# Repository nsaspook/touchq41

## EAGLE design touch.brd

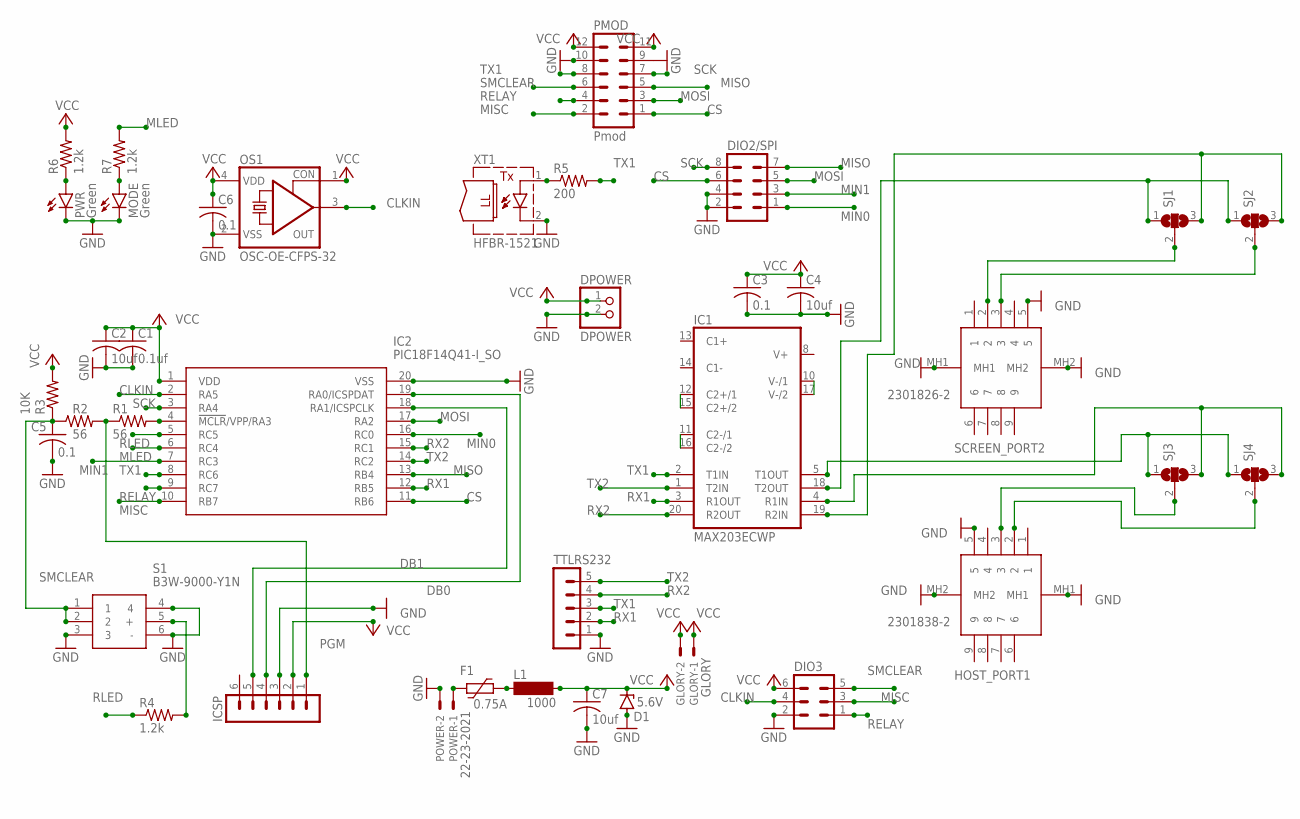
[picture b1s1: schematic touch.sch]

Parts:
C1: 0.1uf; C0805
C2, C4, C7: 10uf; C0805
C3, C5, C6: 0.1; C0805
D1: 5.6V; SMB
DIO2/SPI: MA04-2
DIO3: MA03-2
DPOWER: DPOWER; 1X02
F1: 0.75A; 1206L
GLORY: GLORY; 22-23-2021
HOST_PORT1: 2301838-2; 23018382
IC1: MAX203ECWP; SO20L
IC2: PIC18F14Q41-I_SO; SOIC127P1030X265-20N
ICSP: MA06-1
L1: 1000; SM-1206
MODE: Green; CHIPLED_1206
OS1: OSC-OE-CFPS-32; 7.2X5.2-4-PAD
PMOD: Pmod; MA06-2
POWER: 22-23-2021
PWR: Green; CHIPLED_1206
R1, R2: 56; R0805
R3: 10K; R0805
R4, R6, R7: 1.2k; R0805
R5: 200; R0805
S1: B3W-9000-Y1N; B3W-9_1-LED
SCREEN_PORT2: 2301826-2; 23018262
SJ1, SJ2, SJ3, SJ4: SJ2W; SJ_2
TTLRS232: MA05-1
XT1: HFBR-1521; HFBR-15X3

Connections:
CLKIN: DIO3.4, IC2.2 (RA5), OS1.3 (OUT)
CS: DIO2/SPI.6, IC2.11 (RB6), PMOD.1
DB0: IC2.19 (RA0/ICSPDAT), ICSP.4
DB1: IC2.18 (RA1/ICSPCLK), ICSP.5
GND: C1.2, C2.2, C3.2, C4.2, C5.2, C6.2, C7.2, D1.A, DIO2/SPI.2, DIO2/SPI.4, DIO3.2, DPOWER.2, HOST_PORT1.5, HOST_PORT1.MH1, HOST_PORT1.MH2, IC1.6 (GND), IC1.9 (GND), IC2.20 (VSS), ICSP.3, MODE.C, OS1.2 (VSS), PMOD.9, PMOD.10, POWER.2, PWR.C, S1.3, S1.4, S1.6 (-), SCREEN_PORT2.5, SCREEN_PORT2.MH1, SCREEN_PORT2.MH2, TTLRS232.1, XT1.2 (C)
MIN0: DIO2/SPI.1, IC2.16 (RC0)
MIN1: DIO2/SPI.3, IC2.7 (RC3)
MISC: DIO3.3, IC2.10 (RB7), PMOD.2
MISO: DIO2/SPI.7, IC2.13 (RB4), PMOD.5
MLED: IC2.6 (RC4), R7.2
MOSI: DIO2/SPI.5, IC2.17 (RA2), PMOD.3
unnamed: SCREEN_PORT2.3, SJ2.2
unnamed: SCREEN_PORT2.2, SJ1.2
unnamed: HOST_PORT1.2, SJ4.2
unnamed: HOST_PORT1.3, SJ3.2
unnamed: IC1.12 (C2+/1), IC1.15 (C2+/2)
unnamed: IC1.11 (C2-/1), IC1.16 (C2-/2)
unnamed: IC1.10 (V-/1), IC1.17 (V-/2)
unnamed: IC1.5 (T1OUT), SJ3.1, SJ4.1
unnamed: IC1.4 (R1IN), SJ3.3, SJ4.3
unnamed: IC1.18 (T2OUT), SJ1.1, SJ2.1
unnamed: IC1.19 (R2IN), SJ1.3, SJ2.3
unnamed: IC2.4 (!MCLR!/VPP/RA3), R1.2
unnamed: F1.2, POWER.1
unnamed: MODE.A, R7.1
unnamed: R4.2, S1.5 (+)
unnamed: R5.1, XT1.1 (A)
unnamed: F1.1, L1.1
unnamed: PWR.A, R6.1
PGM: ICSP.1, R1.1, R2.2
RELAY: DIO3.1, IC2.9 (RC7), PMOD.4
RLED: IC2.5 (RC5), R4.1
RX1: IC1.3 (R1OUT), IC2.12 (RB5), TTLRS232.2
RX2: IC1.20 (R2OUT), IC2.15 (RC1), TTLRS232.4
SCK: DIO2/SPI.8, IC2.3 (RA4), PMOD.7
SMCLEAR: C5.1, DIO3.5, PMOD.6, R2.1, R3.1, S1.1, S1.2
TX1: IC1.2 (T1IN), IC2.8 (RC6), PMOD.8, R5.2, TTLRS232.3
TX2: IC1.1 (T2IN), IC2.14 (RC2), TTLRS232.5
VCC: C1.1, C2.1, C3.1, C4.1, C6.1, C7.1, D1.C, DIO3.6, DPOWER.1, GLORY.1, GLORY.2, IC1.7 (VCC), IC2.1 (VDD), ICSP.2, L1.2, OS1.1 (CON), OS1.4 (VDD), PMOD.11, PMOD.12, R3.2, R6.2

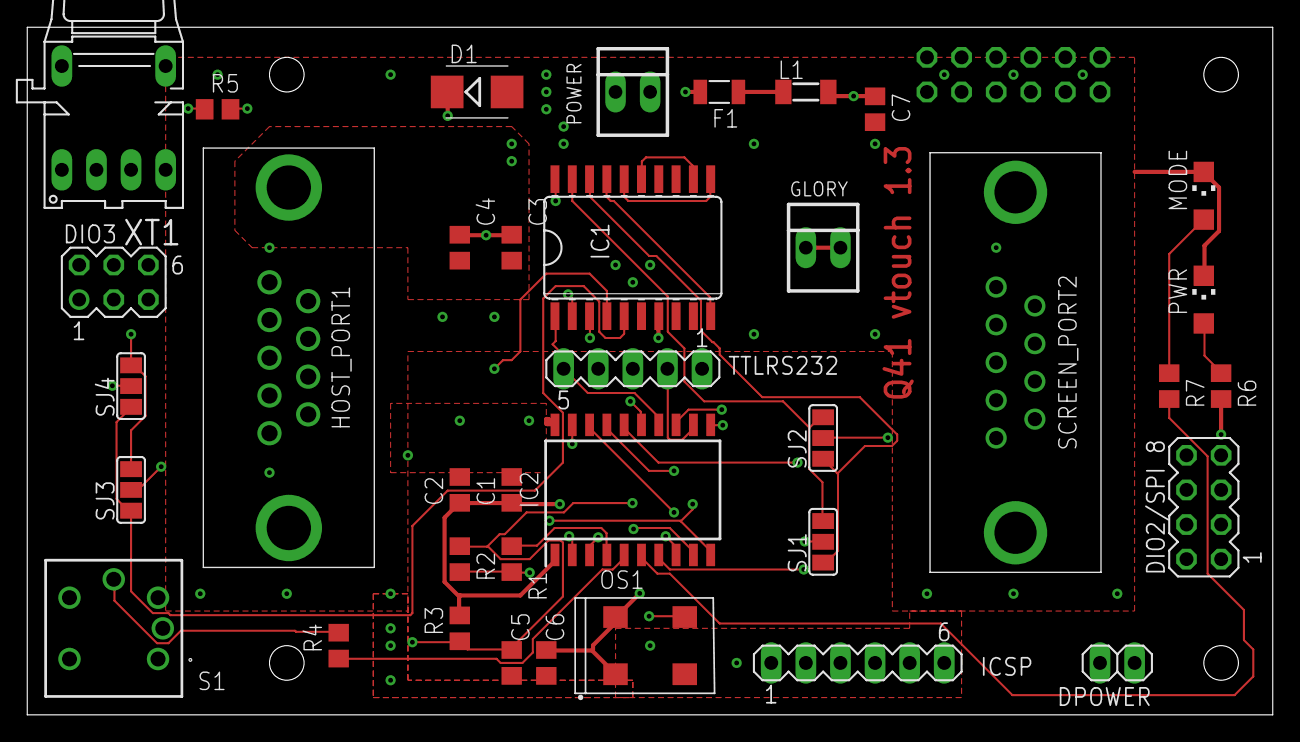
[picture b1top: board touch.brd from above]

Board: 4 copper layers, 91.4 x 50.5 mm, 38 parts (1 on the bottom side), 39 nets.

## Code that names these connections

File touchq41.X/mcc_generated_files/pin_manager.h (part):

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// get/set IO_RA0 aliases
#define IO_RA0_TRIS                 TRISAbits.TRISA0
#define IO_RA0_LAT                  LATAbits.LATA0
#define IO_RA0_PORT                 PORTAbits.RA0
#define IO_RA0_WPU                  WPUAbits.WPUA0
#define IO_RA0_OD                   ODCONAbits.ODCA0
#define IO_RA0_ANS                  ANSELAbits.ANSELA0
#define IO_RA0_SetHigh()            do { LATAbits.LATA0 = 1; } while(0)
#define IO_RA0_SetLow()             do { LATAbits.LATA0 = 0; } while(0)
#define IO_RA0_Toggle()             do { LATAbits.LATA0 = ~LATAbits.LATA0; } while(0)
#define IO_RA0_GetValue()           PORTAbits.RA0
#define IO_RA0_SetDigitalInput()    do { TRISAbits.TRISA0 = 1; } while(0)
#define IO_RA0_SetDigitalOutput()   do { TRISAbits.TRISA0 = 0; } while(0)
#define IO_RA0_SetPullup()          do { WPUAbits.WPUA0 = 1; } while(0)
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// get/set IO_RA1 aliases
#define IO_RA1_TRIS                 TRISAbits.TRISA1
#define IO_RA1_LAT                  LATAbits.LATA1
#define IO_RA1_PORT                 PORTAbits.RA1
#define IO_RA1_WPU                  WPUAbits.WPUA1
#define IO_RA1_OD                   ODCONAbits.ODCA1
#define IO_RA1_ANS                  ANSELAbits.ANSELA1
#define IO_RA1_SetHigh()            do { LATAbits.LATA1 = 1; } while(0)
#define IO_RA1_SetLow()             do { LATAbits.LATA1 = 0; } while(0)
#define IO_RA1_Toggle()             do { LATAbits.LATA1 = ~LATAbits.LATA1; } while(0)
#define IO_RA1_GetValue()           PORTAbits.RA1
#define IO_RA1_SetDigitalInput()    do { TRISAbits.TRISA1 = 1; } while(0)
#define IO_RA1_SetDigitalOutput()   do { TRISAbits.TRISA1 = 0; } while(0)
#define IO_RA1_SetPullup()          do { WPUAbits.WPUA1 = 1; } while(0)
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#define RA2_SetHigh()            do { LATAbits.LATA2 = 1; } while(0)
#define RA2_SetLow()             do { LATAbits.LATA2 = 0; } while(0)
#define RA2_Toggle()             do { LATAbits.LATA2 = ~LATAbits.LATA2; } while(0)
#define RA2_GetValue()              PORTAbits.RA2
#define RA2_SetDigitalInput()    do { TRISAbits.TRISA2 = 1; } while(0)
#define RA2_SetDigitalOutput()   do { TRISAbits.TRISA2 = 0; } while(0)
#define RA2_SetPullup()             do { WPUAbits.WPUA2 = 1; } while(0)
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#define RA4_SetHigh()            do { LATAbits.LATA4 = 1; } while(0)
#define RA4_SetLow()             do { LATAbits.LATA4 = 0; } while(0)
#define RA4_Toggle()             do { LATAbits.LATA4 = ~LATAbits.LATA4; } while(0)
#define RA4_GetValue()              PORTAbits.RA4
#define RA4_SetDigitalInput()    do { TRISAbits.TRISA4 = 1; } while(0)
#define RA4_SetDigitalOutput()   do { TRISAbits.TRISA4 = 0; } while(0)
#define RA4_SetPullup()             do { WPUAbits.WPUA4 = 1; } while(0)
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#define RB4_SetHigh()            do { LATBbits.LATB4 = 1; } while(0)
#define RB4_SetLow()             do { LATBbits.LATB4 = 0; } while(0)
#define RB4_Toggle()             do { LATBbits.LATB4 = ~LATBbits.LATB4; } while(0)
#define RB4_GetValue()              PORTBbits.RB4
#define RB4_SetDigitalInput()    do { TRISBbits.TRISB4 = 1; } while(0)
#define RB4_SetDigitalOutput()   do { TRISBbits.TRISB4 = 0; } while(0)
#define RB4_SetPullup()             do { WPUBbits.WPUB4 = 1; } while(0)
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#define RB5_SetHigh()            do { LATBbits.LATB5 = 1; } while(0)
#define RB5_SetLow()             do { LATBbits.LATB5 = 0; } while(0)
#define RB5_Toggle()             do { LATBbits.LATB5 = ~LATBbits.LATB5; } while(0)
#define RB5_GetValue()              PORTBbits.RB5
#define RB5_SetDigitalInput()    do { TRISBbits.TRISB5 = 1; } while(0)
#define RB5_SetDigitalOutput()   do { TRISBbits.TRISB5 = 0; } while(0)
#define RB5_SetPullup()             do { WPUBbits.WPUB5 = 1; } while(0)
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// get/set CS aliases
#define CS_TRIS                 TRISBbits.TRISB6
#define CS_LAT                  LATBbits.LATB6
#define CS_PORT                 PORTBbits.RB6
#define CS_WPU                  WPUBbits.WPUB6
#define CS_OD                   ODCONBbits.ODCB6
#define CS_ANS                  ANSELBbits.ANSELB6
#define CS_SetHigh()            do { LATBbits.LATB6 = 1; } while(0)
#define CS_SetLow()             do { LATBbits.LATB6 = 0; } while(0)
#define CS_Toggle()             do { LATBbits.LATB6 = ~LATBbits.LATB6; } while(0)
#define CS_GetValue()           PORTBbits.RB6
#define CS_SetDigitalInput()    do { TRISBbits.TRISB6 = 1; } while(0)
#define CS_SetDigitalOutput()   do { TRISBbits.TRISB6 = 0; } while(0)
#define CS_SetPullup()          do { WPUBbits.WPUB6 = 1; } while(0)
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// get/set IO_RB7 aliases
#define IO_RB7_TRIS                 TRISBbits.TRISB7
#define IO_RB7_LAT                  LATBbits.LATB7
#define IO_RB7_PORT                 PORTBbits.RB7
#define IO_RB7_WPU                  WPUBbits.WPUB7
#define IO_RB7_OD                   ODCONBbits.ODCB7
#define IO_RB7_ANS                  ANSELBbits.ANSELB7
#define IO_RB7_SetHigh()            do { LATBbits.LATB7 = 1; } while(0)
#define IO_RB7_SetLow()             do { LATBbits.LATB7 = 0; } while(0)
#define IO_RB7_Toggle()             do { LATBbits.LATB7 = ~LATBbits.LATB7; } while(0)
#define IO_RB7_GetValue()           PORTBbits.RB7
#define IO_RB7_SetDigitalInput()    do { TRISBbits.TRISB7 = 1; } while(0)
#define IO_RB7_SetDigitalOutput()   do { TRISBbits.TRISB7 = 0; } while(0)
#define IO_RB7_SetPullup()          do { WPUBbits.WPUB7 = 1; } while(0)
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// get/set MIN0 aliases
#define MIN0_TRIS                 TRISCbits.TRISC0
#define MIN0_LAT                  LATCbits.LATC0
#define MIN0_PORT                 PORTCbits.RC0
#define MIN0_WPU                  WPUCbits.WPUC0
#define MIN0_OD                   ODCONCbits.ODCC0
#define MIN0_ANS                  ANSELCbits.ANSELC0
#define MIN0_SetHigh()            do { LATCbits.LATC0 = 1; } while(0)
#define MIN0_SetLow()             do { LATCbits.LATC0 = 0; } while(0)
#define MIN0_Toggle()             do { LATCbits.LATC0 = ~LATCbits.LATC0; } while(0)
#define MIN0_GetValue()           PORTCbits.RC0
#define MIN0_SetDigitalInput()    do { TRISCbits.TRISC0 = 1; } while(0)
#define MIN0_SetDigitalOutput()   do { TRISCbits.TRISC0 = 0; } while(0)
#define MIN0_SetPullup()          do { WPUCbits.WPUC0 = 1; } while(0)
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#define RC1_SetHigh()            do { LATCbits.LATC1 = 1; } while(0)
#define RC1_SetLow()             do { LATCbits.LATC1 = 0; } while(0)
#define RC1_Toggle()             do { LATCbits.LATC1 = ~LATCbits.LATC1; } while(0)
#define RC1_GetValue()              PORTCbits.RC1
#define RC1_SetDigitalInput()    do { TRISCbits.TRISC1 = 1; } while(0)
#define RC1_SetDigitalOutput()   do { TRISCbits.TRISC1 = 0; } while(0)
#define RC1_SetPullup()             do { WPUCbits.WPUC1 = 1; } while(0)
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#define RC2_SetHigh()            do { LATCbits.LATC2 = 1; } while(0)
#define RC2_SetLow()             do { LATCbits.LATC2 = 0; } while(0)
#define RC2_Toggle()             do { LATCbits.LATC2 = ~LATCbits.LATC2; } while(0)
#define RC2_GetValue()              PORTCbits.RC2
#define RC2_SetDigitalInput()    do { TRISCbits.TRISC2 = 1; } while(0)
#define RC2_SetDigitalOutput()   do { TRISCbits.TRISC2 = 0; } while(0)
#define RC2_SetPullup()             do { WPUCbits.WPUC2 = 1; } while(0)
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// get/set MIN1 aliases
#define MIN1_TRIS                 TRISCbits.TRISC3
#define MIN1_LAT                  LATCbits.LATC3
#define MIN1_PORT                 PORTCbits.RC3
#define MIN1_WPU                  WPUCbits.WPUC3
#define MIN1_OD                   ODCONCbits.ODCC3
#define MIN1_ANS                  ANSELCbits.ANSELC3
#define MIN1_SetHigh()            do { LATCbits.LATC3 = 1; } while(0)
#define MIN1_SetLow()             do { LATCbits.LATC3 = 0; } while(0)
#define MIN1_Toggle()             do { LATCbits.LATC3 = ~LATCbits.LATC3; } while(0)
#define MIN1_GetValue()           PORTCbits.RC3
#define MIN1_SetDigitalInput()    do { TRISCbits.TRISC3 = 1; } while(0)
#define MIN1_SetDigitalOutput()   do { TRISCbits.TRISC3 = 0; } while(0)
#define MIN1_SetPullup()          do { WPUCbits.WPUC3 = 1; } while(0)
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// get/set MLED aliases
#define MLED_TRIS                 TRISCbits.TRISC4
#define MLED_LAT                  LATCbits.LATC4
#define MLED_PORT                 PORTCbits.RC4
#define MLED_WPU                  WPUCbits.WPUC4
#define MLED_OD                   ODCONCbits.ODCC4
#define MLED_ANS                  ANSELCbits.ANSELC4
#define MLED_SetHigh()            do { LATCbits.LATC4 = 1; } while(0)
#define MLED_SetLow()             do { LATCbits.LATC4 = 0; } while(0)
#define MLED_Toggle()             do { LATCbits.LATC4 = ~LATCbits.LATC4; } while(0)
#define MLED_GetValue()           PORTCbits.RC4
#define MLED_SetDigitalInput()    do { TRISCbits.TRISC4 = 1; } while(0)
#define MLED_SetDigitalOutput()   do { TRISCbits.TRISC4 = 0; } while(0)
#define MLED_SetPullup()          do { WPUCbits.WPUC4 = 1; } while(0)
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// get/set RLED aliases
#define RLED_TRIS                 TRISCbits.TRISC5
#define RLED_LAT                  LATCbits.LATC5
#define RLED_PORT                 PORTCbits.RC5
#define RLED_WPU                  WPUCbits.WPUC5
#define RLED_OD                   ODCONCbits.ODCC5
#define RLED_ANS                  ANSELCbits.ANSELC5
#define RLED_SetHigh()            do { LATCbits.LATC5 = 1; } while(0)
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

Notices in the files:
touchq41.X/mcc_generated_files/pin_manager.h:
(c) 2018 Microchip Technology Inc. and its subsidiaries.
